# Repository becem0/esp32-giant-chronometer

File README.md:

# ⏱️ ESP32 Giant 24V COB LED Chronometer & Industrial PCB

[-orange.svg)]()

An end-to-end industrial-grade embedded system featuring a **6-digit giant 7-segment display** driven by high-lumen **24V COB LED strips**, a custom modular **KiCad 10 PCB**, an **ESP32-WROVER-E** dual-core controller hosting an asynchronous real-time Web dashboard, and **SIM800L GSM cellular telemetry**.

Designed, developed, and fabricated by **[Bacem AMEUR](https://github.com/becem0)** (National Engineering School of Monastir - ENIM) during an engineering internship at **Chrono Sports Events**.

---

## 📸 Hardware Showcase & Gallery

<p align="center">
  <br>
  <em>Figure 1: Photorealistic 3D CAD render of the assembled CHRONO_01 board in KiCad 10.</em>
</p>

<p align="center">
  <br>
  <em>Figure 2: Complete electrical schematic (ESP32, 74HC595 cascade, ULN2803A drivers, LM2596 power regulation).</em>
</p>

<p align="center">
  
  <br>
  <em>Figure 3: Double-sided physical PCB fabricated via chemical etching (Left: Component side F.Cu, Right: Solder side B.Cu).</em>
</p>

---

## 📑 Table of Contents
- [Hardware Showcase & Gallery](#-hardware-showcase--gallery)
- [Key Features](#-key-features)
- [System Architecture](#-system-architecture)
- [Hardware & Electrical Engineering](#-hardware--electrical-engineering)
- [Firmware & Dual-Core Architecture](#-firmware--dual-core-architecture)
- [Web Dashboard UI](#-web-dashboard-ui)
- [Repository Structure](#-repository-structure)
- [Bill of Materials (BOM) & Economic Study](#-bill-of-materials-bom--economic-study)
- [Installation & Getting Started](#-installation--getting-started)
- [Author & License](#-author--license)

---

## 🌟 Key Features

* **High-Visibility Giant Display:** 6 digits (`HH:MM:SS`) using high-density 24V COB LED strips for uniform, neon-like illumination without individual LED hotspots.
* **Dual-Core Asynchronous Firmware:**
  * **Core 0:** Manages Wi-Fi Soft-AP (`SSID: CHRONO_01`) and serves an asynchronous HTML5/CSS3/JavaScript dark-mode web application via `ESPAsyncWebServer`.
  * **Core 1:** Executes deterministic $1\,\text{ms}$ chronometer counting, high-speed SPI shift register cascading, and non-blocking UART GSM AT parsing.
* **High-Power Common-Anode Driving:** 6 daisy-chained `74HC595` serial shift registers interfaced with 6 `ULN2803A` Darlington sink arrays, controlling 42 independent 24V segments at up to $500\,\text{mA}$ per channel.
* **GSM/SMS Telemetry:** Integrated `SIM800L` cellular transceiver with a customized $1000\,\mu\text{F}$ low-ESR reservoir network to absorb 2.0A TDMA RF burst current drops.
* **Cost Efficiency:** Sourced and built for approximately **740 TND (~€220)**, delivering performance comparable to turnkey commercial race scoreboards costing **3,000 to 20,000 TND**.

---

## 🏛 System Architecture

```text
 ┌─────────────────────────────────────────────────────────────────────────────┐
 │                               MAIN POWER SUPPLY                             │
 │                        (230V AC  ──>  24V DC / 2.5A SMPS)                   │
 └──────────────────────┬────────────────────────────────┬─────────────────────┘
                        │ (+24V Power Bus)               │ (+24V Input)
                        ▼                                ▼
       ┌─────────────────────────────────┐      ┌──────────────────────────────┐
       │   42x 24V COB LED SEGMENTS      │      │   LM2596 BUCK REGULATOR      │
       │   (6 Digits: A, B, C, D, E, F, G│      │   (24V DC  ──>  5.0V / 4.1V) │
       │    Common Anode Configuration)  │      └──────────────┬───────────────┘
       └────────────────▲────────────────┘                     │
                        │ Sinking Grounds (x42)                │
       ┌────────────────┴────────────────┐                     ▼
       │     6x ULN2803A DARLINGTON      │             ┌───────────────┐
       │        TRANSISTOR ARRAYS        │◄── 5V ──────┤  ESP32-WROVER │
       └────────────────▲────────────────┘             │   DUAL-CORE   │
                        │ 8-bit Parallel Out (x6)      │  (Soft-AP Web │
       ┌────────────────┴────────────────┐             │   Server +    │
       │       6x 74HC595 SERIAL         │◄── SPI ─────┤   FreeRTOS)   │
       │        SHIFT REGISTERS          │ (DATA/CLK/  └───────┬───────┘
       └─────────────────────────────────┘   LATCH)            │ UART (TX2/RX2)
                                                               ▼
                                                       ┌───────────────┐
                                                       │ SIM800L GSM   │
                                                       │ (+1000uF Cap) │
                                                       └───────────────┘
```

---

## ⚡ Hardware & Electrical Engineering

### I/O Expansion & Power Driving
Driving 42 discrete LED segments using only 3 GPIO pins from the ESP32:
* **`74HC595` Shift Registers:** Cascaded in series. The serial frame ($6 \times 8 = 48\,\text{bits}$) is clocked via high-speed SPI in less than $5\,\mu\text{s}$.
* **`ULN2803A` Darlington Sink Drivers:** 8 open-collector channels with integrated clamp diodes per IC. Each output can sink up to $500\,\text{mA}$ under $24\,\text{V}$, perfectly matching the common-anode COB LED segments.

```text
 ESP32 GPIO ────> 74HC595 (Qn) ───[2.7kΩ]───> ULN2803A (Base) ───> Sinks (-24V) to GND
                                                                           ▲
                                                  +24V Rail ───[LED Strip]─┘
```

### Mathematical Sizing & Transient Filtering
The GSM module consumes up to $I_{\text{peak}} = 2.0\,\text{A}$ in $577\,\mu\text{s}$ bursts. Without adequate capacitive reservoir sizing, the voltage droops below $3.7\,\text{V}$, causing brownout resets.

The required charge buffer is sized according to:
$$C_1 = \frac{I_{\text{peak}} \cdot \Delta t}{\Delta V_{\text{max}}} = \frac{2.0\,\text{A} \times 577\,\mu\text{s}}{0.4\,\text{V}} \approx 2885\,\mu\text{F}$$

Accounting for active source replenishment from the LM2596 buck converter, an effective capacitor of **$1000\,\mu\text{F}$ / 16V low-ESR** in parallel with a **$100\,\text{nF}$ ceramic decoupling capacitor** is placed directly at the SIM800L power pins.

### Single-Sided / NPTH PCB Optimization
To support artisan local PCB chemical etching without plated through-holes (NPTH):
* **Modular T-Shape Topology:** Eliminates track congestion and prevents layer crossing.
* **Machined-Pin Tulip Sockets:** DIP sockets are elevated above the PCB top copper layer to allow top-side manual soldering with fine iron tips.
* **Merged Drill Files:** Excellon drill files configured with "Merge PTH and NPTH" for single-pass fabrication.

---

## 💻 Firmware & Dual-Core Architecture

The firmware is written in Arduino C++ utilizing ESP32 FreeRTOS multitasking:

| Task | Core Assigned | Priority | Execution Interval | Role |
|---|---|---|---|---|
| **`WebNetworkTask`** | **Core 0** | Priority 1 | Asynchronous | Handles Wi-Fi Soft-AP client connections, REST endpoints (`/api/start`, `/api/pause`, `/api/reset`, `/api/set`), and serves HTML5 assets from SPIFFS/Flash. |
| **`ChronometerEngine`** | **Core 1** | Priority 3 | $1.00\,\text{ms}$ deterministic | Hardware timer tick accumulation, 7-segment digit lookup encoding, SPI shifting, and non-blocking SIM800L AT command parsing. |

---

## 📱 Web Dashboard UI

The responsive dark-theme dashboard runs entirely embedded within the ESP32 SPIFFS memory:
* **Zero Internet Required:** Automatically hosts a local hotspot `CHRONO_01` (192.168.4.1).
* **Live Synchronized Display:** CSS seven-segment digital display mirroring the real physical board.
* **Controls:** Start, Pause, Lap Time, Split Time, Time Preset, and Display Brightness.

---

## 📂 Repository Structure

```text
├── .gitignore
├── LICENSE
├── README.md
├── firmware/
│   ├── ChronoServer/
│   │   ├── ChronoServer.ino         # Main dual-core ESP32 firmware
│   │   └── index.html               # Embedded HTML5/CSS3/JS dashboard
│   └── tests/
│       ├── test_blink_esp32.ino     # GPIO & RTC validation test
│       └── test_sim800l_at.ino      # Hardware UART GSM pass-through test
├── hardware/
│   ├── kicad/                       # KiCad 10 schematics (.kicad_sch) and PCB (.kicad_pcb)
│   ├── gerbers/                     # Production Gerber and Excellon drill files
│   ├── schematics/
│   │   └── pinout_reference.md      # Pinout table for JST & shift registers
│   ├── bom/
│   │   └── bill_of_materials.md     # Detailed BOM and supplier breakdown
│   └── mechanical/
│       └── chassis_assembly.md      # Chassis drilling, baffles, and wiring guide
└── docs/
    ├── Journal stage 2026.pdf       # 30-day chronological internship journal
    ├── rapport_stage_2026.pdf       # Compiled official internship engineering report
    ├── stage_chrono_presentation.pdf # Oral defense slide deck
    └── report/
        ├── rapport_stage_bacem_ameur.tex # LaTeX source code
        └── figures/                 # High-resolution schematics, 3D renders & photos
```

---

## 💰 Bill of Materials (BOM) & Economic Study

| Category | Key Items | Cost (TND) | Approx. (€) |
|---|---|---|---|
| **Processing & Telemetry** | ESP32-WROVER-E + SIM800L GSM + LM2596 Buck | ~90 TND | ~€26 |
| **Power Drivers & Logic** | 6x 74HC595 + 6x ULN2803A + Tulip DIP sockets | ~60 TND | ~€18 |
| **Display & Illumination** | 24V COB LED Strips (10m) + JST-XH harnesses | ~100 TND | ~€29 |
| **Power Supply** | S-60-24 SMPS (230V AC $\to$ 24V DC / 2.5A) | ~55 TND | ~€16 |
| **Structure & Enclosure** | Forex (PVC) backplate + Opal PMMA acrylic diffuser | ~80 TND | ~€24 |
| **PCB & Consumables** | Chemical double-sided etching (120 TND), solder, capacitors, wiring | ~355 TND | ~€105 |
| **TOTAL PROJECT INVESTMENT** | | **~740 TND** | **~€220** |
| **Commercial Equivalent Price** | Turnkey 6-digit wireless race chronometers | **3,000 – 20,000 TND** | **€900 – €6,000** |

---

## 🚀 Installation & Getting Started

### 1. Arduino IDE Setup
1. Install **Arduino IDE 2.x**.
2. Install the **ESP32 Board Package** (Recommended: stable version `2.0.17` via Boards Manager).
3. Board Configuration:
   * **Board:** `ESP32 Wrover Module` (or `ESP32 Dev Module`)
   * **Flash Mode:** `DIO` (or `QIO` depending on flash vendor)
   * **Flash Frequency:** `40MHz`
   * **PSRAM:** `Enabled`
   * **Partition Scheme:** `Default 4MB with spiffs`
4. Install required libraries:
   * `ESPAsyncWebServer` & `AsyncTCP`

### 2. Flashing the Firmware
1. Connect the ESP32 to your PC via a Micro-USB data cable.
2. Open `firmware/ChronoServer/ChronoServer.ino`.
3. Select your COM port and hit **Upload** (➔).

### 3. Connecting to the Web Dashboard
1. Power on the chronometer with 24V DC.
2. On your phone or laptop, connect to the Wi-Fi network:
   * **SSID:** `CHRONO_01`
   * **Password:** `12345678`
3. Open any web browser and navigate to:
   * **`http://192.168.4.1`**

---

## 👤 Author

**Bacem AMEUR**  
*Electrical Engineering Student — National Engineering School of Monastir (ENIM)*  
* 📍 Sfax / Monastir, Tunisia  
* 💼 LinkedIn: [linkedin.com/in/becem-ameur](https://linkedin.com/in/becem-ameur)  
* 🐙 GitHub: [@becem0](https://github.com/becem0)  
* ✉️ Email: [Becemameur15@gmail.com](mailto:Becemameur15@gmail.com)

---

## 📜 License
This project is open-source and licensed under the [MIT License](LICENSE).

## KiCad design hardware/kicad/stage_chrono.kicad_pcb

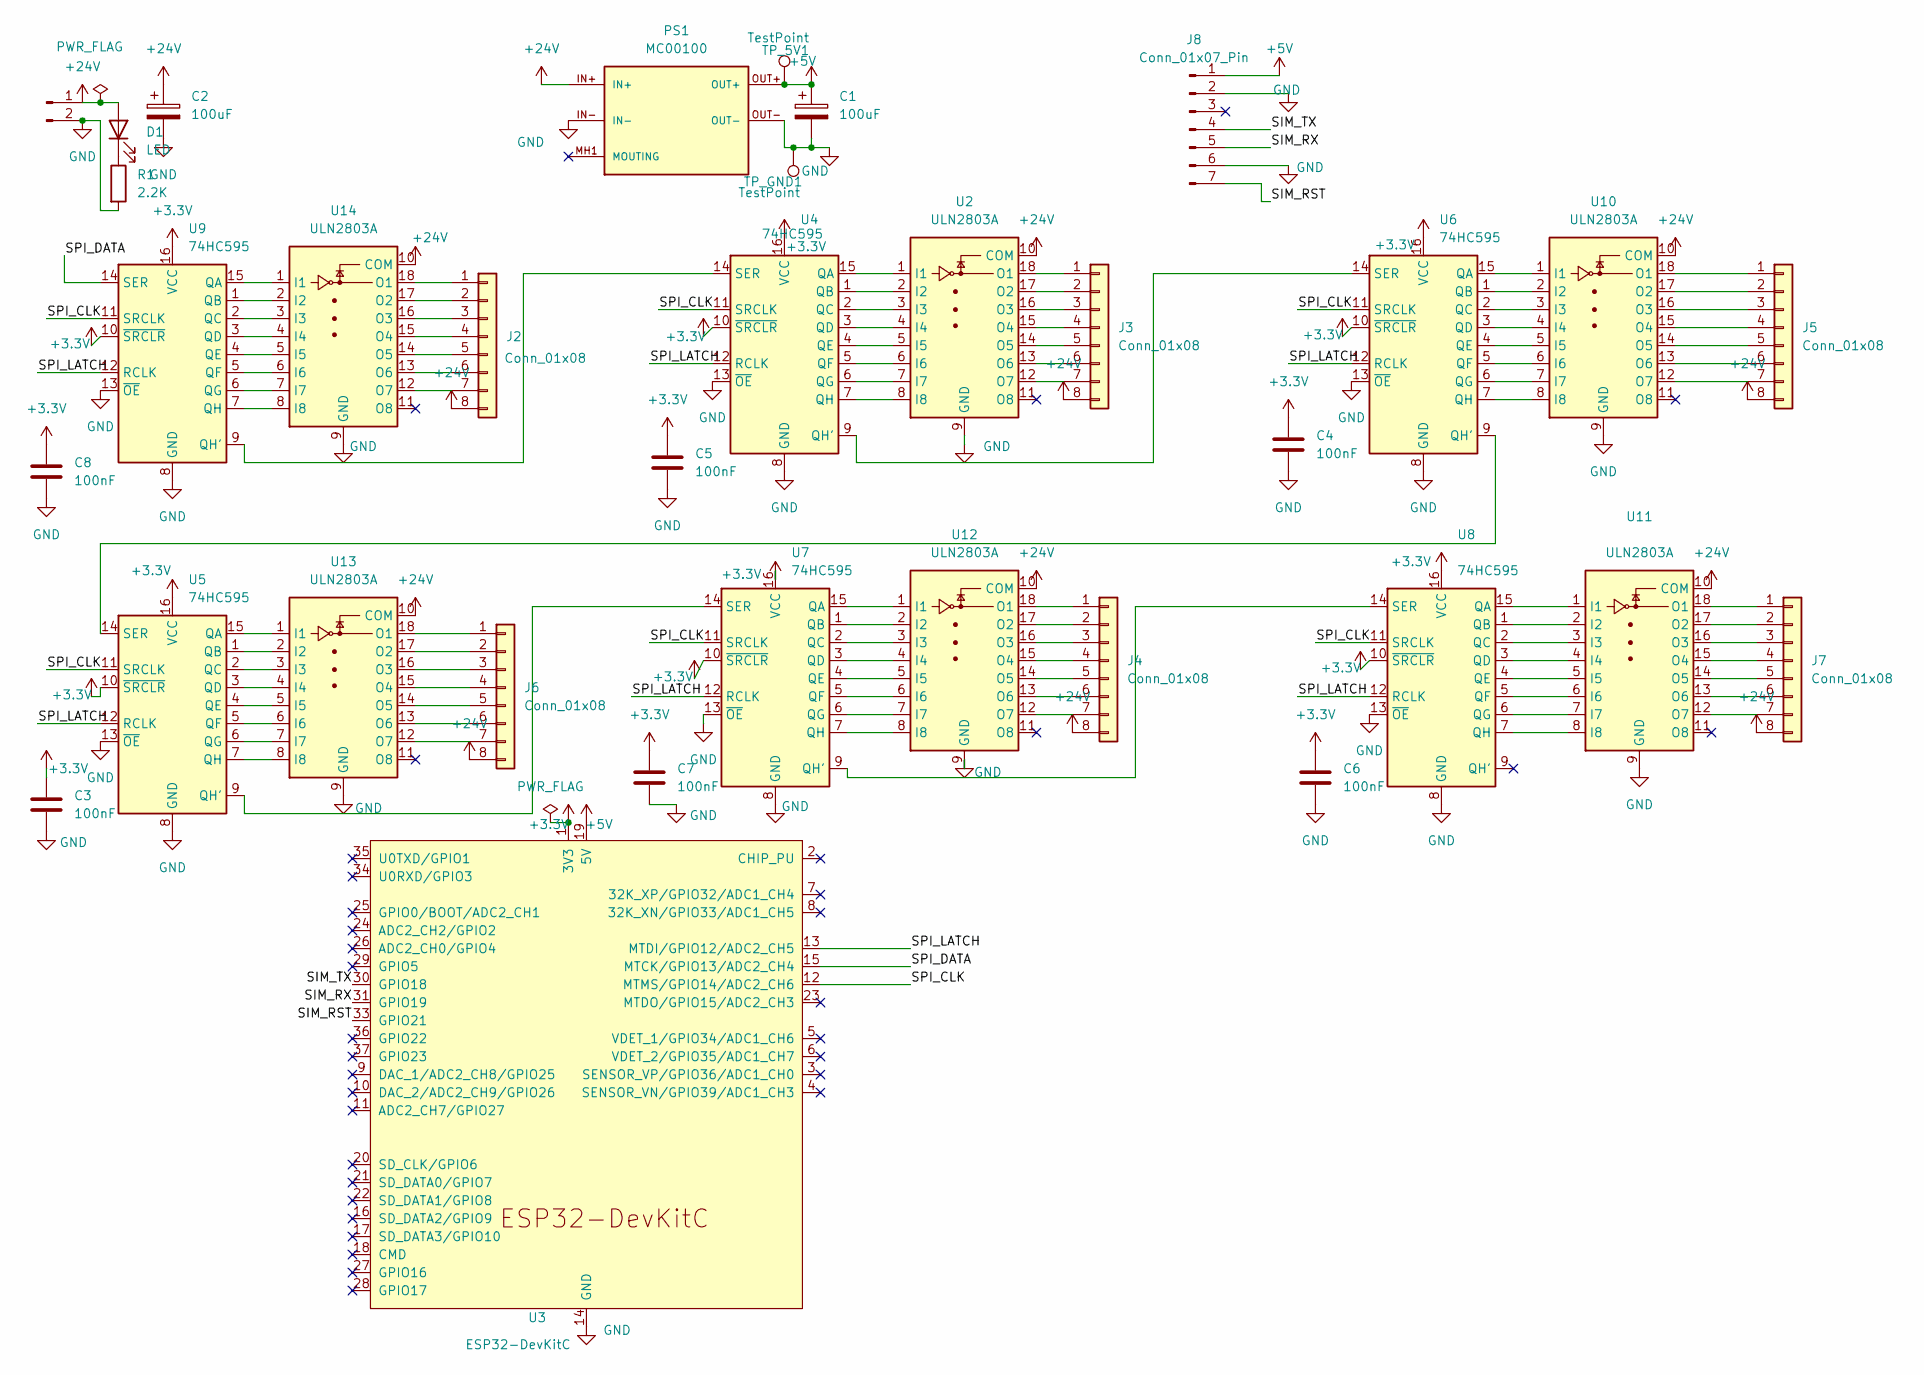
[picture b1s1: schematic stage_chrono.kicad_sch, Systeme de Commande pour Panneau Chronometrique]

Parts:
C1, C2: 100uF; CP_Radial_D8.0mm_P3.50mm
C3, C4, C5, C6, C7, C8: 100nF; C_Disc_D5.0mm_W2.5mm_P5.00mm
D1: LED; LED_D3.0mm
J1: 24_IN; TerminalBlock_Phoenix_MKDS-1,5-2-5.08_1x02_P5.08mm_Horizont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
J2, J3, J4, J5, J6, J7: Conn_01x08; JST_XH_B8B-XH-A_1x08_P2.50mm_Vertical
J8: Conn_01x07_Pin; PinSocket_1x07_P2.54mm_Vertical
PS1: MC00100; CONV_MC00100; PARTREV NA
R1: 2.2K; R_Axial_DIN0207_L6.3mm_D2.5mm_P7.62mm_Horizontal
TP_5V1: TestPoint; TestPoint_Pad_D1.5mm
TP_GND1: TestPoint; TestPoint_Pad_D1.5mm
U2, U10, U11, U12, U13, U14: ULN2803A; DIP-18_W7.62mm
U3: ESP32-DevKitC
U4, U5, U6, U7, U8, U9: 74HC595; DIP-16_W7.62mm

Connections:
+3.3V: C3.1, C4.1, C5.1, C6.1, C7.1, C8.1, U3.1 (3V3), U4.10 (~SRCLR), U4.16 (VCC), U5.10 (~SRCLR), U5.16 (VCC), U6.10 (~SRCLR), U6.16 (VCC), U7.10 (~SRCLR), U7.16 (VCC), U8.10 (~SRCLR), U8.16 (VCC), U9.10 (~SRCLR), U9.16 (VCC)
+5V: C1.1, J8.1, PS1.OUT+, TP_5V1.1 (1_1), U3.19 (5V)
+24V: C2.1, D1.2 (A), J1.1, J2.8, J3.8, J4.8, J5.8, J6.8, J7.8, PS1.IN+, U2.10 (COM), U10.10 (COM), U11.10 (COM), U12.10 (COM), U13.10 (COM), U14.10 (COM)
/SIM_RST: J8.7, U3.33 (GPIO21)
/SIM_RX: J8.5, U3.31 (GPIO19)
/SIM_TX: J8.4, U3.30 (GPIO18)
/SPI_CLK: U3.12 (MTMS/GPIO14/ADC2_CH6), U4.11 (SRCLK), U5.11 (SRCLK), U6.11 (SRCLK), U7.11 (SRCLK), U8.11 (SRCLK), U9.11 (SRCLK)
/SPI_DATA: U3.15 (MTCK/GPIO13/ADC2_CH4), U9.14 (SER)
/SPI_LATCH: U3.13 (MTDI/GPIO12/ADC2_CH5), U4.12 (RCLK), U5.12 (RCLK), U6.12 (RCLK), U7.12 (RCLK), U8.12 (RCLK), U9.12 (RCLK)
GND: C1.2, C2.2, C3.2, C4.2, C5.2, C6.2, C7.2, C8.2, J1.2, J8.2, J8.6, PS1.IN-, PS1.OUT-, R1.2, TP_GND1.1 (1_1), U2.9 (GND), U3.14 (GND), U3.32 (GND), U3.38 (GND), U4.8 (GND), U4.13 (~OE), U5.8 (GND), U5.13 (~OE), U6.8 (GND), U6.13 (~OE), U7.8 (GND), U7.13 (~OE), U8.8 (GND), U8.13 (~OE), U9.8 (GND), U9.13 (~OE), U10.9 (GND), U11.9 (GND), U12.9 (GND), U13.9 (GND), U14.9 (GND)
unnamed: D1.1 (K), R1.1
unnamed: J2.1, U14.18 (O1)
unnamed: J2.2, U14.17 (O2)
unnamed: J2.3, U14.16 (O3)
unnamed: J2.4, U14.15 (O4)
unnamed: J2.5, U14.14 (O5)
unnamed: J2.6, U14.13 (O6)
unnamed: J2.7, U14.12 (O7)
unnamed: J3.1, U2.18 (O1)
unnamed: J3.2, U2.17 (O2)
unnamed: J3.3, U2.16 (O3)
unnamed: J3.4, U2.15 (O4)
unnamed: J3.5, U2.14 (O5)
unnamed: J3.6, U2.13 (O6)
unnamed: J3.7, U2.12 (O7)
unnamed: J4.1, U12.18 (O1)
unnamed: J4.2, U12.17 (O2)
unnamed: J4.3, U12.16 (O3)
unnamed: J4.4, U12.15 (O4)
unnamed: J4.5, U12.14 (O5)
unnamed: J4.6, U12.13 (O6)
unnamed: J4.7, U12.12 (O7)
unnamed: J5.1, U10.18 (O1)
unnamed: J5.2, U10.17 (O2)
unnamed: J5.3, U10.16 (O3)
unnamed: J5.4, U10.15 (O4)
unnamed: J5.5, U10.14 (O5)
unnamed: J5.6, U10.13 (O6)
unnamed: J5.7, U10.12 (O7)
unnamed: J6.1, U13.18 (O1)
unnamed: J6.2, U13.17 (O2)
unnamed: J6.3, U13.16 (O3)
unnamed: J6.4, U13.15 (O4)
unnamed: J6.5, U13.14 (O5)
unnamed: J6.6, U13.13 (O6)
unnamed: J6.7, U13.12 (O7)
unnamed: J7.1, U11.18 (O1)
unnamed: J7.2, U11.17 (O2)
unnamed: J7.3, U11.16 (O3)
unnamed: J7.4, U11.15 (O4)
unnamed: J7.5, U11.14 (O5)
unnamed: J7.6, U11.13 (O6)
unnamed: J7.7, U11.12 (O7)
unnamed: U2.1 (I1), U4.15 (QA)
unnamed: U2.2 (I2), U4.1 (QB)
unnamed: U2.3 (I3), U4.2 (QC)
unnamed: U2.4 (I4), U4.3 (QD)
unnamed: U2.5 (I5), U4.4 (QE)
unnamed: U2.6 (I6), U4.5 (QF)
unnamed: U2.7 (I7), U4.6 (QG)
unnamed: U2.8 (I8), U4.7 (QH)
unnamed: U4.9 (QH'), U6.14 (SER)
unnamed: U4.14 (SER), U9.9 (QH')
unnamed: U5.9 (QH'), U7.14 (SER)
unnamed: U5.14 (SER), U6.9 (QH')
unnamed: U7.9 (QH'), U8.14 (SER)
unnamed: U6.15 (QA), U10.1 (I1)
unnamed: U6.1 (QB), U10.2 (I2)
unnamed: U6.2 (QC), U10.3 (I3)
unnamed: U6.3 (QD), U10.4 (I4)
unnamed: U6.4 (QE), U10.5 (I5)
unnamed: U6.5 (QF), U10.6 (I6)
unnamed: U6.6 (QG), U10.7 (I7)
unnamed: U6.7 (QH), U10.8 (I8)
unnamed: U8.15 (QA), U11.1 (I1)
unnamed: U8.1 (QB), U11.2 (I2)
unnamed: U8.2 (QC), U11.3 (I3)
unnamed: U8.3 (QD), U11.4 (I4)
unnamed: U8.4 (QE), U11.5 (I5)
unnamed: U8.5 (QF), U11.6 (I6)
unnamed: U8.6 (QG), U11.7 (I7)
unnamed: U8.7 (QH), U11.8 (I8)
unnamed: U7.15 (QA), U12.1 (I1)
unnamed: U7.1 (QB), U12.2 (I2)
unnamed: U7.2 (QC), U12.3 (I3)
unnamed: U7.3 (QD), U12.4 (I4)
unnamed: U7.4 (QE), U12.5 (I5)
unnamed: U7.5 (QF), U12.6 (I6)
unnamed: U7.6 (QG), U12.7 (I7)
unnamed: U7.7 (QH), U12.8 (I8)
unnamed: U5.15 (QA), U13.1 (I1)
unnamed: U5.1 (QB), U13.2 (I2)
unnamed: U5.2 (QC), U13.3 (I3)
unnamed: U5.3 (QD), U13.4 (I4)
unnamed: U5.4 (QE), U13.5 (I5)
unnamed: U5.5 (QF), U13.6 (I6)
unnamed: U5.6 (QG), U13.7 (I7)
unnamed: U5.7 (QH), U13.8 (I8)
unnamed: U9.15 (QA), U14.1 (I1)
unnamed: U9.1 (QB), U14.2 (I2)
unnamed: U9.2 (QC), U14.3 (I3)
unnamed: U9.3 (QD), U14.4 (I4)
unnamed: U9.4 (QE), U14.5 (I5)
unnamed: U9.5 (QF), U14.6 (I6)
unnamed: U9.6 (QG), U14.7 (I7)
unnamed: U9.7 (QH), U14.8 (I8)

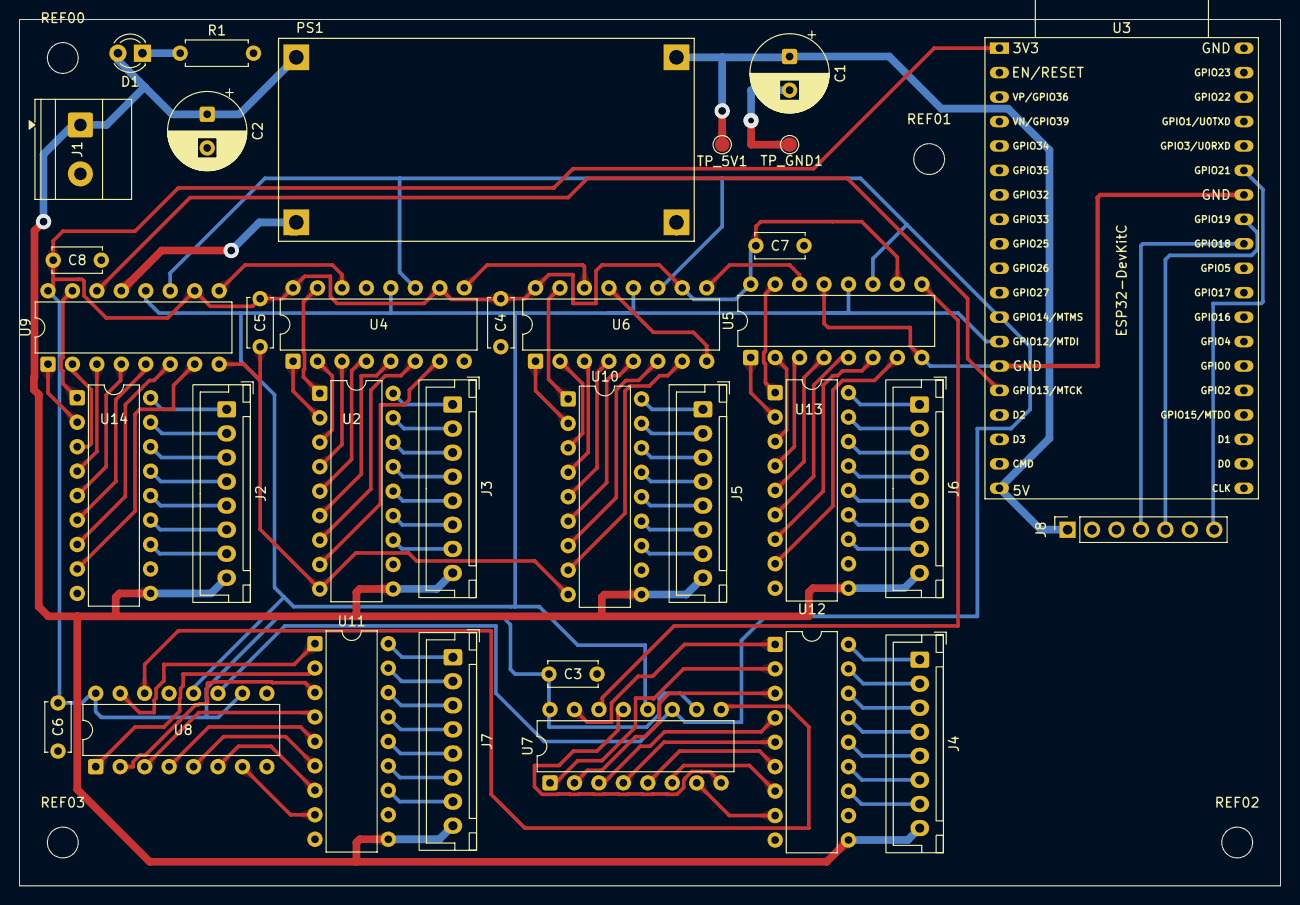
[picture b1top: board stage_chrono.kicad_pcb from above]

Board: 2 copper layers, 131.0 x 90.0 mm, 38 parts (0 on the bottom side), 106 nets.

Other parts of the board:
REF00, REF01, REF02, REF03: MountingHole_3.2mm_M3

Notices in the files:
README.md:
License: MIT
